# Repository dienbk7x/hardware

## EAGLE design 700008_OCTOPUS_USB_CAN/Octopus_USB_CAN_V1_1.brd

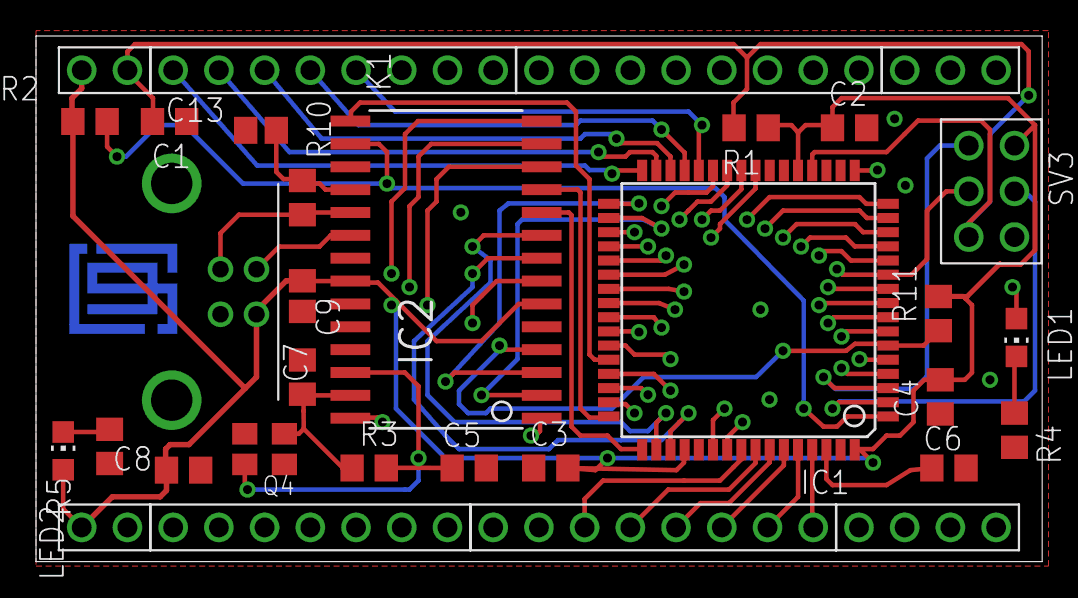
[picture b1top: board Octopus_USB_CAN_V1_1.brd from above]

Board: 4 copper layers, 55.9 x 29.2 mm, 33 parts (1 on the bottom side), 64 nets.

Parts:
C1, C2, C3, C4, C6, C7: 100nF; C0805
C5, C9: 22pF; C0805
C8, C13: 2.2uF; C0805
IC1: AT90CAN128; TQFP64
IC2: USBN9604; SO28-3
JP1, JP2, JP4: 61300811121
JP3: 61300711121
JP5: 61300311121
JP7: 61300411121
JP8, JP11: 61300211121
K1: 61400416121
LED1: ROT; CHIP-LED0805
LED2: GRUEN; CHIP-LED0805
Q4: 16 MHz; SX-32
R1, R2, R11: 10K; R0805
R3: 1M; R0805
R4, R5: 270R; R0805
R10: 1K5; R0805
SV3: 61300621121
U$1: EPLOGO; EPLOGOKUPFER

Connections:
CLKOUT: IC1.24, IC2.28
D+: IC2.19, K1.3, R10.2
D-: IC2.20, K1.2
GND: C1.1, C2.2, C3.1, C4.1, C5.1, C6.2, C7.1, C8.2, C9.1, C13.1, IC1.22, IC1.53, IC1.63, IC2.17, IC2.21, IC2.23, IC2.24, IC2.25, JP8.2, K1.4, R4.2, R5.2, SV3.6
unnamed: C6.1, IC1.62
unnamed: C9.2, IC2.27, Q4.1, R3.1
unnamed: C13.2, IC2.18, R10.1
unnamed: LED1.C, R4.1
unnamed: LED2.C, R5.1
unnamed: C5.2, IC2.26, Q4.3, R3.2
PA0: IC1.51, IC2.8
PA1: IC1.50, IC2.9
PA2: IC1.49, IC2.10
PA3: IC1.48, IC2.11
PA4: IC1.47, IC2.12
PA5: IC1.46, IC2.13
PA6: IC1.45, IC2.14
PA7: IC1.44, IC2.15
PB0: IC1.10, JP2.8
PB1: IC1.11, JP2.7, SV3.2
PB2: IC1.12, JP2.6
PB3: IC1.13, JP2.5
PB4: IC1.14, JP2.4
PB5: IC1.15, JP2.3
PB6: IC1.16, JP2.2
PB7: IC1.17, JP2.1, LED1.A
PC0: IC1.35, JP3.7
PC1: IC1.36, JP3.6
PC2: IC1.37, JP3.5
PC3: IC1.38, JP3.4
PC4: IC1.39, JP3.3
PC5: IC1.40, JP3.2
PC6: IC1.41, JP3.1
PC7: IC1.42, IC2.1
PD0: IC1.25, JP1.8
PD1: IC1.26, JP1.7
PD2: IC1.27, JP1.6
PD3: IC1.28, JP1.5
PD4: IC1.29, JP1.4
PD5: IC1.30, JP1.3
PD6: IC1.31, JP1.2
PD7: IC1.32, JP1.1
PE0: IC1.2, JP7.4, SV3.5
PE1: IC1.3, JP7.3, SV3.1
PE2: IC1.4, JP7.2
PE3: IC1.5, JP7.1
PE4: IC1.6, IC2.4, R11.1
PE5: IC1.7, JP5.3
PE6: IC1.8, JP5.2
PE7: IC1.9, JP5.1
PF0: IC1.61, JP4.1
PF1: IC1.60, JP4.2
PF2: IC1.59, JP4.3
PF3: IC1.58, JP4.4
PF4: IC1.57, JP4.5
PF5: IC1.56, JP4.6
PF6: IC1.55, JP4.7
PF7: IC1.54, JP4.8
PG0: IC1.33, IC2.3
PG1: IC1.34, IC2.2
PG2: IC1.43, IC2.7
PG5: IC1.1, IC2.16, R2.1
RES: C1.2, IC1.20, JP11.2, R1.2, SV3.3
VCC: C2.1, C3.2, C4.2, C7.2, C8.1, IC1.21, IC1.52, IC1.64, IC2.6, IC2.22, JP8.1, JP11.1, K1.1, LED2.A, R1.1, R2.2, R11.2, SV3.4

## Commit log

2013-08-20 add octopus can schematic
